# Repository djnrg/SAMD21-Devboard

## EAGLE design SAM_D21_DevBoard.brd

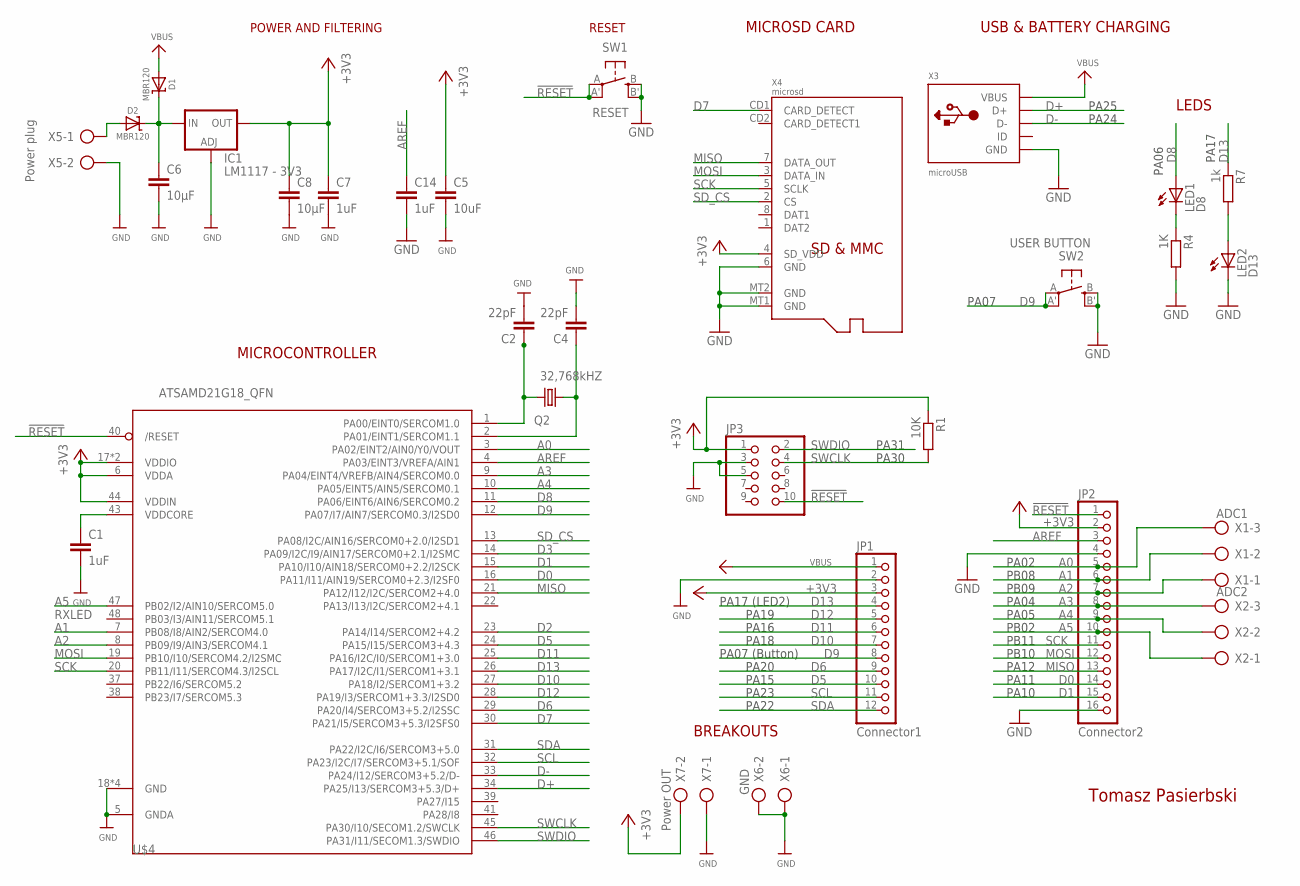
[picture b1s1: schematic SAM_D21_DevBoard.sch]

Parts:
C1, C7, C14: 1uF; C1206
C2, C4: 22pF; C1206
C5: 10uF; C1206
C6, C8: 10µF; C1206
D1, D2: MBR120; SOD-123
IC1: LM1117 - 3V3; SOT223
JP1: Connector1; 1X12
JP2: Connector2; 1X16
JP3: PINHD-2X5; 2X05
LED1: D8; 1206
LED2: D13; 1206
Q2: 32,768kHZ; HC49UP
R1: 10K; M1206
R4: 1K; M1206
R7: 1k; M1206
SW1: RESET; EVQ-Q2
SW2: USER BUTTON; EVQ-Q2
U$4: ATSAMD21G18_QFN; TQFN48_7MM
X1: ADC1; AK300/3
X2: ADC2; AK300/3
X3: microUSB; 4UCONN_20329_V2
X4: microsd; MICROSD
X5: Power plug; AK300/2
X6: GND; AK300/2
X7: Power OUT; AK300/2

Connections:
!RESET: JP2.1, JP3.10, SW1.A, SW1.A' (P1), U$4.40 (/RESET)
+3V3: C5.1, C7.1, C8.1, IC1.4 (OUT), JP1.3, JP2.2, JP3.1, R1.1, U$4.6 (VDDA), U$4.17 (VDDIO), U$4.36 (VDDIO), U$4.44 (VDDIN), X4.4 (SD_VDD), X7.2
A0: JP2.5, U$4.3 (PA02/EINT2/AIN0/Y0/VOUT), X1.3
A1: JP2.6, U$4.7 (PB08/I8/AIN2/SERCOM4.0), X1.2
A2: JP2.7, U$4.8 (PB09/I9/AIN3/SERCOM4.1), X1.1
A3: JP2.8, U$4.9 (PA04/EINT4/VREFB/AIN4/SERCOM0.0), X2.3
A4: JP2.9, U$4.10 (PA05/EINT5/AIN5/SERCOM0.1), X2.2
A5: JP2.10, U$4.47 (PB02/I2/AIN10/SERCOM5.0), X2.1
AREF: C14.1, JP2.3, U$4.4 (PA03/EINT3/VREFA/AIN1)
D0: JP2.14, U$4.16 (PA11/I11/AIN19/SERCOM0+2.3/I2SF0)
D1: JP2.15, U$4.15 (PA10/I10/AIN18/SERCOM0+2.2/I2SCK)
D2: U$4.23 (PA14/I14/SERCOM2+4.2)
D3: U$4.14 (PA09/I2C/I9/AIN17/SERCOM0+2.1/I2SMC)
D5: JP1.10, U$4.24 (PA15/I15/SERCOM3+4.3)
D6: JP1.9, U$4.29 (PA20/I4/SERCOM3+5.2/I2SSC)
D7: U$4.30 (PA21/I5/SERCOM3+5.3/I2SFS0), X4.CD1 (CARD_DETECT)
D8: LED1.A, U$4.11 (PA06/EINT6/AIN6/SERCOM0.2)
D9: JP1.8, SW2.A, SW2.A' (P1), U$4.12 (PA07/I7/AIN7/SERCOM0.3/I2SD0)
D10: JP1.7, U$4.27 (PA18/I2/SERCOM1+3.2)
D11: JP1.6, U$4.25 (PA16/I2C/I0/SERCOM1+3.0)
D12: JP1.5, U$4.28 (PA19/I3/SERCOM1+3.3/I2SD0)
D13: JP1.4, R7.1, U$4.26 (PA17/I2C/I1/SERCOM1+3.1)
D+: U$4.34 (PA25/I13/SERCOM3+5.3/D+), X3.D+
D-: U$4.33 (PA24/I12/SERCOM3+5.2/D-), X3.D-
GND: C1.2, C2.2, C4.2, C5.2, C6.2, C7.2, C8.2, C14.2, IC1.1 (ADJ), JP1.2, JP2.4, JP2.16, JP3.3, JP3.5, LED2.C, R4.2, SW1.B (S), SW1.B' (S1), SW2.B (S), SW2.B' (S1), U$4.5 (GNDA), U$4.18 (GND), U$4.35 (GND), U$4.42 (GND), U$4.THERMAL (GND), X3.BASE@1 (GND), X3.BASE@2 (GND), X3.GND, X3.SPRT@1 (GND), X3.SPRT@2 (GND), X3.SPRT@3 (GND), X3.SPRT@4 (GND), X4.6 (GND), X4.MT1 (GND), X4.MT2 (GND), X5.2, X6.1, X6.2, X7.1
MISO: JP2.13, U$4.21 (PA12/I12/I2C/SERCOM2+4.0), X4.7 (DATA_OUT)
MOSI: JP2.12, U$4.19 (PB10/I10/SERCOM4.2/I2SMC), X4.3 (DATA_IN)
unnamed: C6.1, D1.C, D2.C, IC1.3 (IN)
unnamed: LED2.A, R7.2
unnamed: D2.A, X5.1
unnamed: C2.1, Q2.2, U$4.1 (PA00/EINT0/SERCOM1.0)
unnamed: LED1.C, R4.1
unnamed: C4.1, Q2.1, U$4.2 (PA01/EINT1/SERCOM1.1)
SCK: JP2.11, U$4.20 (PB11/I11/SERCOM4.3/I2SCL), X4.5 (SCLK)
SCL: JP1.11, U$4.32 (PA23/I2C/I7/SERCOM3+5.1/SOF)
SDA: JP1.12, U$4.31 (PA22/I2C/I6/SERCOM3+5.0)
SD_CS: U$4.13 (PA08/I2C/AIN16/SERCOM0+2.0/I2SD1), X4.2 (CS)
SWCLK: JP3.4, R1.2, U$4.45 (PA30/I10/SECOM1.2/SWCLK)
SWDIO: JP3.2, U$4.46 (PA31/I11/SECOM1.3/SWDIO)
VBUS: D1.A, JP1.1, X3.VBUS
VDDCORE: C1.1, U$4.43 (VDDCORE)

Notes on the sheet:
POWER AND FILTERING
RESET
RXLED
USB & BATTERY CHARGING
MICROSD CARD
BREAKOUTS
LEDS
MICROCONTROLLER
PA07
PA06
PA17
PA25
PA24
PA30
PA31
PA17 (LED2)
PA19
PA16
PA18
PA07 (Button)
PA20
PA15
PA23
PA22
PA02
PB08
PB09
PA04
PA05
PB02
PB11
PB10
PA12
PA11
PA10
Tomasz Pasierbski

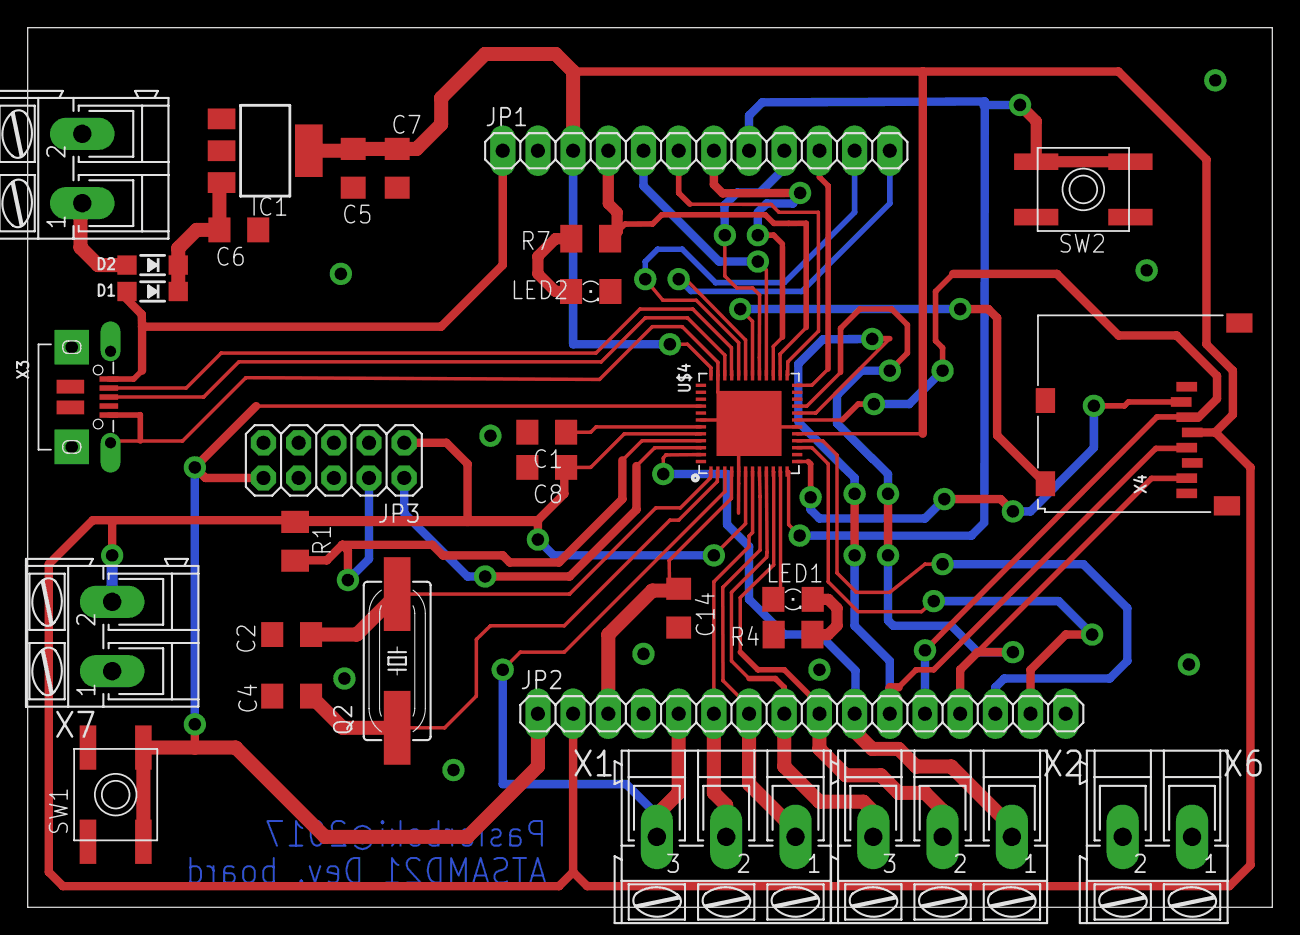
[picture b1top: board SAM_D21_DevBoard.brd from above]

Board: 2 copper layers, 89.8 x 63.5 mm, 30 parts (0 on the bottom side), 39 nets.

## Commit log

2018-12-01 Initial file upload
    Last version before manufacturing

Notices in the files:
parts and their libraries:
microbuilder: This work is placed in the public domain, and may be freely used for commercial and non-commercial work with the following conditions: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
